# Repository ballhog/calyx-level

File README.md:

# Calyx-Level

Wired, fail-safe auto top-off (ATO) for a reef system. Part of the Corallite **Calyx** family
(wired connected devices: Calyx-Outlet, Calyx-Sense, Calyx-Level).

Built for Joe's own tank first. Each step should be useful on its own; it becomes a product only if it proves itself.

## In one paragraph

A **sensor node** at the sump reads the water level and the RO reservoir, and while water is needed it keeps
handing a short **run permission (lease)** over Ethernet to a **pump node** at the RO station. The pump node runs
the pump only while it holds a fresh lease and stays inside its own limits (run time, off time, daily volume).
Anything that breaks (cable, switch, either node, firmware) makes the lease run out and the pump stop. A
**hardwired high-level float** cuts pump power in series, with no firmware or network in the path. Both nodes are
Olimex ESP32-POE-ISO boards on a blank Arduino Uno proto shield, so off-the-shelf Uno shields plug straight in.

## Docs

| Doc | What's in it |
|---|---|
| [docs/design.md](docs/design.md) | How it works: roles, lease protocol, limits, sensor health, failure table, reporting |
| [docs/parts.md](docs/parts.md) | Parts list (bench build and per node), with what's already on hand |
| [docs/schematic.md](docs/schematic.md) | Wiring, pin map (Uno names ↔ ESP32 GPIO), input/output circuits, power |
| [docs/provisioning.md](docs/provisioning.md) | First flash, node role and id, Coeno OTA, publishing builds |
| [hardware/DESIGN.md](hardware/DESIGN.md) | KiCad carrier rev A: schematic, PCB, build options, checks before ordering |

## Status (2026-10-26)

Carrier PCB rev A designed (schematic + routed board, DRC copper-clean; see hardware/DESIGN.md). No firmware yet. Coeno already serves `/firmware/calyx-level/latest.json` (Coeno `b9fa573`).

## Related

- Corallite project docs: *Corallite ATO - architecture 2026-10-22* (the decisions this repo implements),
  *Corallite doser - E4 controller 2026-10-22*, *Salt swap doser - parked 2026-10-20*.
- [ballhog/calyx-sense](https://github.com/ballhog/calyx-sense): same board family, same OTA client.
- Coeno `firmware/calyx-level/` and `coeno/api/routes/firmware.py`: the OTA server.

## Rules that don't bend

1. Safety lives on the boxes. Xanthe and Coeno read and alert; they never switch the pump.
2. The high-level cutoff is hardware in series with pump power. It is never a shield input or a firmware decision.
3. No network message ever means "run". Only a fresh lease does, and silence means stop.

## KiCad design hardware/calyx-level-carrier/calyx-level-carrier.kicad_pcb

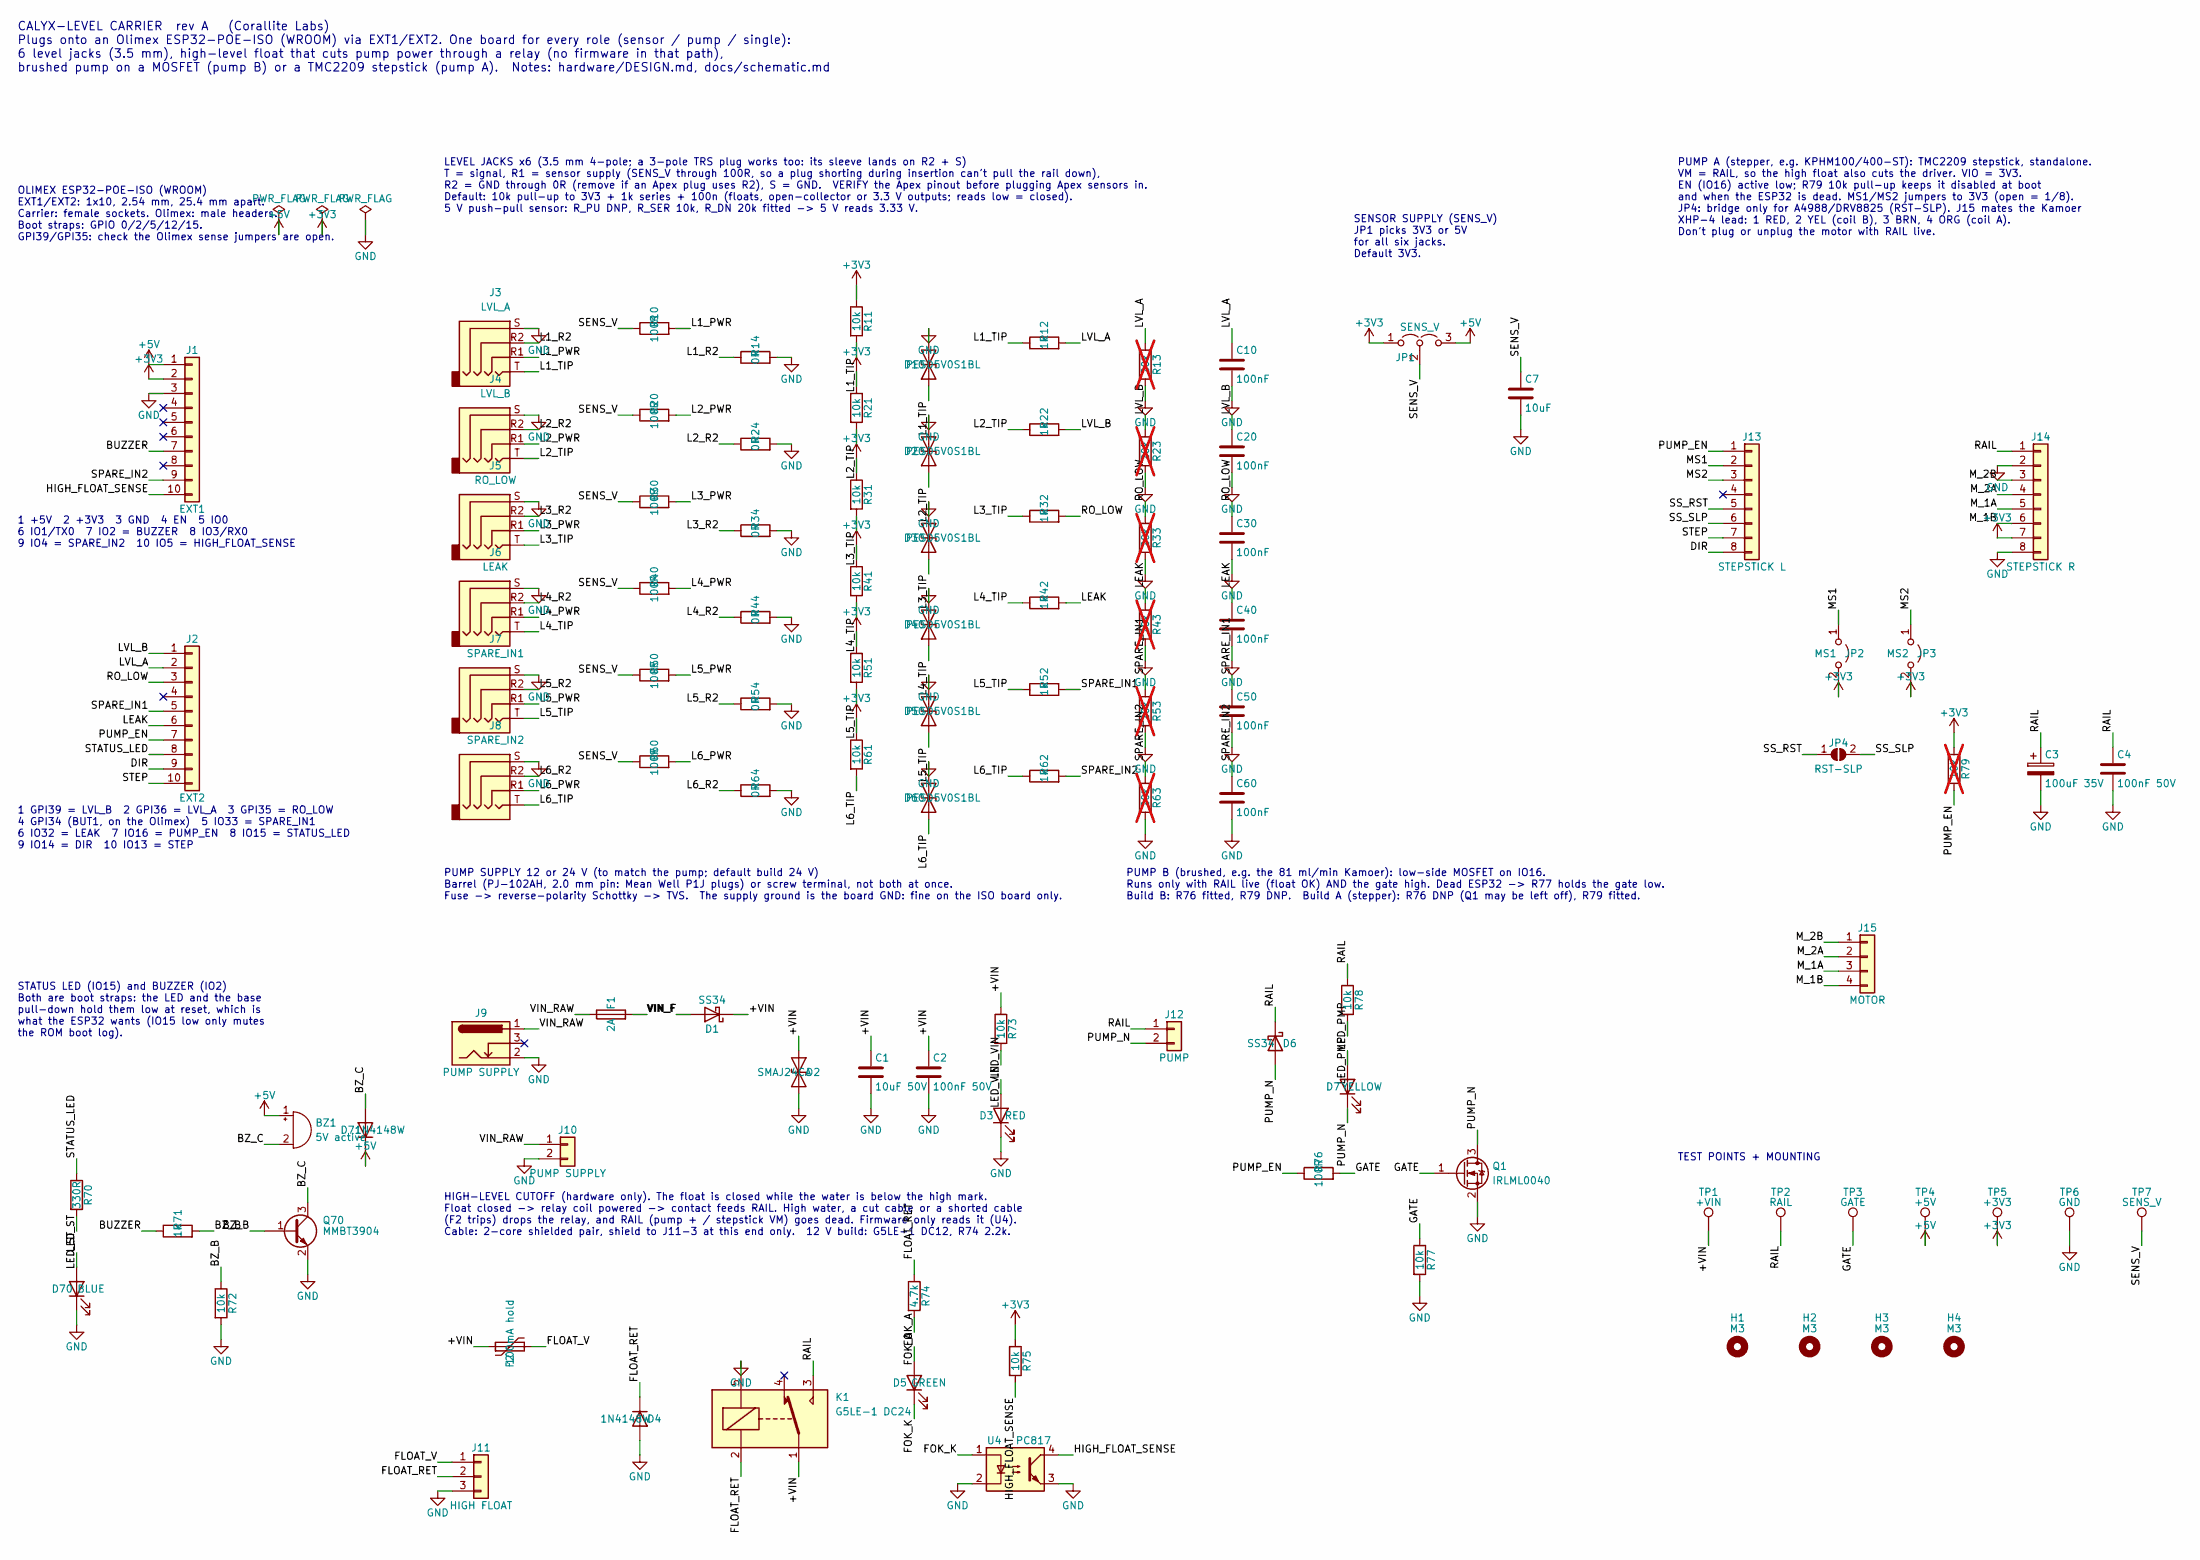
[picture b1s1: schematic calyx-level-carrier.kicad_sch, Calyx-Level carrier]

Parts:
BZ1: 5V active; Buzzer_12x9.5RM7.6; MPN PUI AI-1223-TWT-5V-2-R (verify: 12 mm, 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
C1: 10uF 50V; C_1206_3216Metric_Pad1.33x1.80mm_HandSolder
C2, C4: 100nF 50V; C_0603_1608Metric_Pad1.08x0.95mm_HandSolder
C3: 100uF 35V; CP_Radial_D6.3mm_P2.50mm
C7: 10uF; C_0805_2012Metric_Pad1.18x1.45mm_HandSolder
C10, C20, C30, C40, C50, C60: 100nF; C_0603_1608Metric_Pad1.08x0.95mm_HandSolder
D1, D6: SS34; D_SMA; MPN SS34
D2: SMAJ24CA; D_SMA; MPN SMAJ24CA
D3: RED; LED_0603_1608Metric
D4, D71: 1N4148W; D_SOD-123
D5: GREEN; LED_0603_1608Metric
D7: YELLOW; LED_0603_1608Metric
D10, D20, D30, D40, D50, D60: PESD5V0S1BL; D_SOD-323; MPN PESD5V0S1BL
D70: BLUE; LED_0603_1608Metric
F1: 2A; Fuseholder_Littelfuse_Nano2_154x; MPN Littelfuse 0154002.DRT holder + 0453002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
F2: 100mA hold; Fuse_1812_4532Metric; MPN Bourns MF-MSMF010-2 (0.1 A, 60 V)
H1, H2, H3, H4: M3; MountingHole_3.2mm_M3
J1: EXT1; PinSocket_1x10_P2.54mm_Vertical
J2: EXT2; PinSocket_1x10_P2.54mm_Vertical
J3: LVL_A; Jack_3.5mm_KoreanHropartsElec_PJ-320D-4A_Horizontal; MPN PJ-320D-4A; LCSC C95562
J4: LVL_B; Jack_3.5mm_KoreanHropartsElec_PJ-320D-4A_Horizontal; MPN PJ-320D-4A; LCSC C95562
J5: RO_LOW; Jack_3.5mm_KoreanHropartsElec_PJ-320D-4A_Horizontal; MPN PJ-320D-4A; LCSC C95562
J6: LEAK; Jack_3.5mm_KoreanHropartsElec_PJ-320D-4A_Horizontal; MPN PJ-320D-4A; LCSC C95562
J7: SPARE_IN1; Jack_3.5mm_KoreanHropartsElec_PJ-320D-4A_Horizontal; MPN PJ-320D-4A; LCSC C95562
J8: SPARE_IN2; Jack_3.5mm_KoreanHropartsElec_PJ-320D-4A_Horizontal; MPN PJ-320D-4A; LCSC C95562
J9: PUMP SUPPLY; BarrelJack_CUI_PJ-102AH_Horizontal; MPN PJ-102AH
J10: PUMP SUPPLY; TerminalBlock_Phoenix_MKDS-1,5-2-5.08_1x02_P5.08mm_Horizont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; MPN MKDS 1,5/2-5,08 (1715721)
J11: HIGH FLOAT; TerminalBlock_Phoenix_MKDS-1,5-3-5.08_1x03_P5.08mm_Horizont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; MPN MKDS 1,5/3-5,08 (1715734)
J12: PUMP; TerminalBlock_Phoenix_MKDS-1,5-2-5.08_1x02_P5.08mm_Horizont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; MPN MKDS 1,5/2-5,08 (1715721)
J13: STEPSTICK L; PinSocket_1x08_P2.54mm_Vertical
J14: STEPSTICK R; PinSocket_1x08_P2.54mm_Vertical
J15: MOTOR; JST_XH_B4B-XH-A_1x04_P2.50mm_Vertical; MPN B4B-XH-A
JP1: SENS_V; PinHeader_1x03_P2.54mm_Vertical
JP2: MS1; PinHeader_1x02_P2.54mm_Vertical
JP3: MS2; PinHeader_1x02_P2.54mm_Vertical
JP4: RST-SLP; SolderJumper-2_P1.3mm_Open_RoundedPad1.0x1.5mm
K1: G5LE-1 DC24; Relay_SPDT_Omron-G5LE-1; MPN G5LE-1 DC24
Q1: IRLML0040; SOT-23; MPN IRLML0040TRPBF
Q70: MMBT3904; SOT-23
R10, R20, R30, R40, R50, R60, R76: 100R; R_0603_1608Metric_Pad0.98x0.95mm_HandSolder
R11, R21, R31, R41, R51, R61, R72, R73, R75, R77, R78: 10k; R_0603_1608Metric_Pad0.98x0.95mm_HandSolder
R12, R22, R32, R42, R52, R62, R71: 1k; R_0603_1608Metric_Pad0.98x0.95mm_HandSolder
R13, R23, R33, R43, R53, R63: 20k; R_0603_1608Metric_Pad0.98x0.95mm_HandSolder; not fitted
R14, R24, R34, R44, R54, R64: 0R; R_0603_1608Metric_Pad0.98x0.95mm_HandSolder
R70: 330R; R_0603_1608Metric_Pad0.98x0.95mm_HandSolder
R74: 4.7k; R_1206_3216Metric_Pad1.30x1.75mm_HandSolder
R79: 10k; R_0603_1608Metric_Pad0.98x0.95mm_HandSolder; not fitted
TP1: +VIN; TestPoint_Pad_D1.5mm
TP2: RAIL; TestPoint_Pad_D1.5mm
TP3: GATE; TestPoint_Pad_D1.5mm
TP4: +5V; TestPoint_Pad_D1.5mm
TP5: +3V3; TestPoint_Pad_D1.5mm
TP6: GND; TestPoint_Pad_D1.5mm
TP7: SENS_V; TestPoint_Pad_D1.5mm
U4: PC817; SMDIP-4_W9.53mm; MPN PC817 SMD gull-wing (verify lead span)

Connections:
+3V3: J1.2, J14.7, JP1.1 (A), JP2.2 (B), JP3.2 (B), R11.1, R21.1, R31.1, R41.1, R51.1, R61.1, R75.1, R79.1, TP5.1
+5V: BZ1.1 (+), D71.1 (K), J1.1, JP1.3 (B), TP4.1
/+VIN: C1.1, C2.1, D1.1 (K), D2.1 (A1), F2.1, K1.1, R73.1, TP1.1
/BUZZER: J1.7, R71.1
/BZ_B: Q70.1 (B), R71.2, R72.1
/BZ_C: BZ1.2 (-), D71.2 (A), Q70.3 (C)
/DIR: J2.9, J13.8
/FLOAT_RET: D4.1 (K), J11.2, K1.2, R74.1
/FLOAT_V: F2.2, J11.1
/FOK_A: D5.2 (A), R74.2
/FOK_K: D5.1 (K), U4.1
/GATE: Q1.1 (G), R76.2, R77.1, TP3.1
/HIGH_FLOAT_SENSE: J1.10, R75.2, U4.4
/L1_PWR: J3.R1, R10.2
/L1_R2: J3.R2, R14.1
/L1_TIP: D10.1 (A1), J3.T, R11.2, R12.1
/L2_PWR: J4.R1, R20.2
/L2_R2: J4.R2, R24.1
/L2_TIP: D20.1 (A1), J4.T, R21.2, R22.1
/L3_PWR: J5.R1, R30.2
/L3_R2: J5.R2, R34.1
/L3_TIP: D30.1 (A1), J5.T, R31.2, R32.1
/L4_PWR: J6.R1, R40.2
/L4_R2: J6.R2, R44.1
/L4_TIP: D40.1 (A1), J6.T, R41.2, R42.1
/L5_PWR: J7.R1, R50.2
/L5_R2: J7.R2, R54.1
/L5_TIP: D50.1 (A1), J7.T, R51.2, R52.1
/L6_PWR: J8.R1, R60.2
/L6_R2: J8.R2, R64.1
/L6_TIP: D60.1 (A1), J8.T, R61.2, R62.1
/LEAK: C40.1, J2.6, R42.2, R43.1
/LED_PMP: D7.2 (A), R78.2
/LED_ST: D70.2 (A), R70.2
/LED_VIN: D3.2 (A), R73.2
/LVL_A: C10.1, J2.2, R12.2, R13.1
/LVL_B: C20.1, J2.1, R22.2, R23.1
/MS1: J13.2, JP2.1 (A)
/MS2: J13.3, JP3.1 (A)
/M_1A: J14.5, J15.3
/M_1B: J14.6, J15.4
/M_2A: J14.4, J15.2
/M_2B: J14.3, J15.1
/PUMP_EN: J2.7, J13.1, R76.1, R79.2
/PUMP_N: D6.2 (A), D7.1 (K), J12.2, Q1.3 (D)
/RAIL: C3.1, C4.1, D6.1 (K), J12.1, J14.1, K1.3, R78.1, TP2.1
/RO_LOW: C30.1, J2.3, R32.2, R33.1
/SENS_V: C7.1, JP1.2 (C), R10.1, R20.1, R30.1, R40.1, R50.1, R60.1, TP7.1
/SPARE_IN1: C50.1, J2.5, R52.2, R53.1
/SPARE_IN2: C60.1, J1.9, R62.2, R63.1
/SS_RST: J13.5, JP4.1 (A)
/SS_SLP: J13.6, JP4.2 (B)
/STATUS_LED: J2.8, R70.1
/STEP: J2.10, J13.7
/VIN_F: D1.2 (A), F1.2
/VIN_RAW: F1.1, J9.1, J10.1
GND: C1.2, C2.2, C3.2, C4.2, C7.2, C10.2, C20.2, C30.2, C40.2, C50.2, C60.2, D2.2 (A2), D3.1 (K), D4.2 (A), D10.2 (A2), D20.2 (A2), D30.2 (A2), D40.2 (A2), D50.2 (A2), D60.2 (A2), D70.1 (K), J1.3, J3.S, J4.S, J5.S, J6.S, J7.S, J8.S, J9.2, J10.2, J11.3, J14.2, J14.8, K1.5, Q1.2 (S), Q70.2 (E), R13.2, R14.2, R23.2, R24.2, R33.2, R34.2, R43.2, R44.2, R53.2, R54.2, R63.2, R64.2, R72.2, R77.2, TP6.1, U4.2, U4.3

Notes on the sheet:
CALYX-LEVEL CARRIER rev A (Corallite Labs) Plugs onto an Olimex ESP32-POE-ISO (WROOM) via EXT1/EXT2. One board for every role (sensor / pump / single): 6 level jacks (3.5 mm), high-level float that cuts pump power through a relay (no firmware in that path), brushed pump on a MOSFET (pump B) or a TM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
OLIMEX ESP32-POE-ISO (WROOM) EXT1/EXT2: 1x10, 2.54 mm, 25.4 mm apart. Carrier: female sockets. Olimex: male headers. Boot straps: GPIO 0/2/5/12/15. GPI39/GPI35: check the Olimex sense jumpers are open.
1 +5V 2 +3V3 3 GND 4 EN 5 IO0 6 IO1/TX0 7 IO2 = BUZZER 8 IO3/RX0 9 IO4 = SPARE_IN2 10 IO5 = HIGH_FLOAT_SENSE
1 GPI39 = LVL_B 2 GPI36 = LVL_A 3 GPI35 = RO_LOW 4 GPI34 (BUT1, on the Olimex) 5 IO33 = SPARE_IN1 6 IO32 = LEAK 7 IO16 = PUMP_EN 8 IO15 = STATUS_LED 9 IO14 = DIR 10 IO13 = STEP
LEVEL JACKS x6 (3.5 mm 4-pole; a 3-pole TRS plug works too: its sleeve lands on R2 + S) T = signal, R1 = sensor supply (SENS_V through 100R, so a plug shorting during insertion can't pull the rail down), R2 = GND through 0R (remove if an Apex plug uses R2), S = GND. VERIFY the Apex pinout before pl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
SENSOR SUPPLY (SENS_V) JP1 picks 3V3 or 5V for all six jacks. Default 3V3.
STATUS LED (IO15) and BUZZER (IO2) Both are boot straps: the LED and the base pull-down hold them low at reset, which is what the ESP32 wants (IO15 low only mutes the ROM boot log).
PUMP SUPPLY 12 or 24 V (to match the pump; default build 24 V) Barrel (PJ-102AH, 2.0 mm pin: Mean Well P1J plugs) or screw terminal, not both at once. Fuse -> reverse-polarity Schottky -> TVS. The supply ground is the board GND: fine on the ISO board only.
HIGH-LEVEL CUTOFF (hardware only). The float is closed while the water is below the high mark. Float closed -> relay coil powered -> contact feeds RAIL. High water, a cut cable or a shorted cable (F2 trips) drops the relay, and RAIL (pump + / stepstick VM) goes dead. Firmware only reads it (U4). Ca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
PUMP B (brushed, e.g. the 81 ml/min Kamoer): low-side MOSFET on IO16. Runs only with RAIL live (float OK) AND the gate high. Dead ESP32 -> R77 holds the gate low. Build B: R76 fitted, R79 DNP. Build A (stepper): R76 DNP (Q1 may be left off), R79 fitted.
PUMP A (stepper, e.g. KPHM100/400-ST): TMC2209 stepstick, standalone. VM = RAIL, so the high float also cuts the driver. VIO = 3V3. EN (IO16) active low; R79 10k pull-up keeps it disabled at boot and when the ESP32 is dead. MS1/MS2 jumpers to 3V3 (open = 1/8). JP4: bridge only for A4988/DRV8825 (RS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
TEST POINTS + MOUNTING

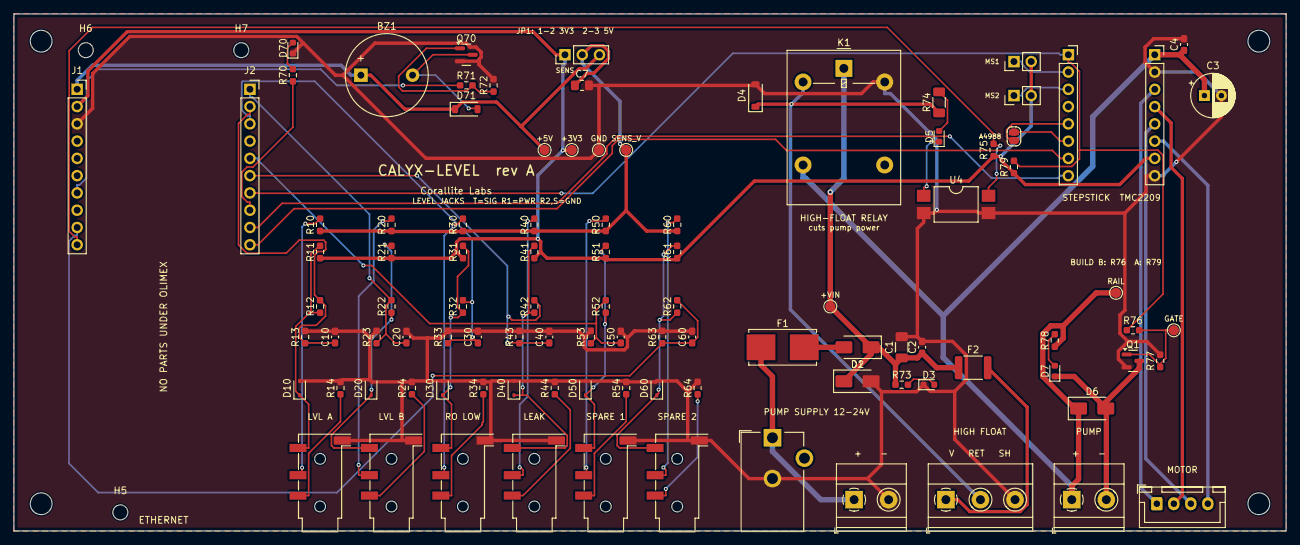
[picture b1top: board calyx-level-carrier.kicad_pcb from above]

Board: 2 copper layers, 187.0 x 76.0 mm, 106 parts (0 on the bottom side), 57 nets.

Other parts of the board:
H5: Olimex MH1 standoff; MountingHole_2.2mm_M2
H6: Olimex MH2 standoff; MountingHole_2.2mm_M2
H7: Olimex MH3 standoff; MountingHole_2.2mm_M2

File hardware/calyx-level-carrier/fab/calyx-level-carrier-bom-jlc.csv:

Comment,Designator,Footprint,LCSC Part #,MPN
5V active,BZ1,Buzzer_12x9.5RM7.6,,"PUI AI-1223-TWT-5V-2-R (verify: 12 mm, 7.6 mm pitch, active 5 V)"
10uF 50V,C1,C_1206_3216Metric_Pad1.33x1.80mm_HandSolder,,
100nF,"C10,C20,C30,C40,C50,C60",C_0603_1608Metric_Pad1.08x0.95mm_HandSolder,,
100nF 50V,"C2,C4",C_0603_1608Metric_Pad1.08x0.95mm_HandSolder,,
100uF 35V,C3,CP_Radial_D6.3mm_P2.50mm,,
10uF,C7,C_0805_2012Metric_Pad1.18x1.45mm_HandSolder,,
SS34,"D1,D6",D_SMA,,SS34
PESD5V0S1BL,"D10,D20,D30,D40,D50,D60",D_SOD-323,,PESD5V0S1BL
SMAJ24CA,D2,D_SMA,,SMAJ24CA
RED,D3,LED_0603_1608Metric,,
1N4148W,"D4,D71",D_SOD-123,,
GREEN,D5,LED_0603_1608Metric,,
YELLOW,D7,LED_0603_1608Metric,,
BLUE,D70,LED_0603_1608Metric,,
2A,F1,Fuseholder_Littelfuse_Nano2_154x,,Littelfuse 0154002.DRT holder + 0453002.MR fuse (verify)
100mA hold,F2,Fuse_1812_4532Metric,,"Bourns MF-MSMF010-2 (0.1 A, 60 V)"
EXT1,J1,PinSocket_1x10_P2.54mm_Vertical,,
PUMP SUPPLY,J10,"TerminalBlock_Phoenix_MKDS-1,5-2-5.08_1x02_P5.08mm_Horizontal",,"MKDS 1,5/2-5,08 (1715721)"
HIGH FLOAT,J11,"TerminalBlock_Phoenix_MKDS-1,5-3-5.08_1x03_P5.08mm_Horizontal",,"MKDS 1,5/3-5,08 (1715734)"
PUMP,J12,"TerminalBlock_Phoenix_MKDS-1,5-2-5.08_1x02_P5.08mm_Horizontal",,"MKDS 1,5/2-5,08 (1715721)"
STEPSTICK L,J13,PinSocket_1x08_P2.54mm_Vertical,,
STEPSTICK R,J14,PinSocket_1x08_P2.54mm_Vertical,,
MOTOR,J15,JST_XH_B4B-XH-A_1x04_P2.50mm_Vertical,,B4B-XH-A
EXT2,J2,PinSocket_1x10_P2.54mm_Vertical,,
LVL_A,J3,Jack_3.5mm_KoreanHropartsElec_PJ-320D-4A_Horizontal,C95562,
LVL_B,J4,Jack_3.5mm_KoreanHropartsElec_PJ-320D-4A_Horizontal,C95562,
RO_LOW,J5,Jack_3.5mm_KoreanHropartsElec_PJ-320D-4A_Horizontal,C95562,
LEAK,J6,Jack_3.5mm_KoreanHropartsElec_PJ-320D-4A_Horizontal,C95562,
SPARE_IN1,J7,Jack_3.5mm_KoreanHropartsElec_PJ-320D-4A_Horizontal,C95562,
SPARE_IN2,J8,Jack_3.5mm_KoreanHropartsElec_PJ-320D-4A_Horizontal,C95562,
PUMP SUPPLY,J9,BarrelJack_CUI_PJ-102AH_Horizontal,,PJ-102AH
SENS_V,JP1,PinHeader_1x03_P2.54mm_Vertical,,
MS1,JP2,PinHeader_1x02_P2.54mm_Vertical,,
MS2,JP3,PinHeader_1x02_P2.54mm_Vertical,,
RST-SLP,JP4,SolderJumper-2_P1.3mm_Open_RoundedPad1.0x1.5mm,,
G5LE-1 DC24,K1,Relay_SPDT_Omron-G5LE-1,,G5LE-1 DC24
IRLML0040,Q1,SOT-23,,IRLML0040TRPBF
MMBT3904,Q70,SOT-23,,
100R,"R10,R20,R30,R40,R50,R60,R76",R_0603_1608Metric_Pad0.98x0.95mm_HandSolder,,
10k,"R11,R21,R31,R41,R51,R61,R72,R73,R75,R77,R78",R_0603_1608Metric_Pad0.98x0.95mm_HandSolder,,
1k,"R12,R22,R32,R42,R52,R62,R71",R_0603_1608Metric_Pad0.98x0.95mm_HandSolder,,
0R,"R14,R24,R34,R44,R54,R64",R_0603_1608Metric_Pad0.98x0.95mm_HandSolder,,
330R,R70,R_0603_1608Metric_Pad0.98x0.95mm_HandSolder,,
4.7k,R74,R_1206_3216Metric_Pad1.30x1.75mm_HandSolder,,
PC817,U4,SMDIP-4_W9.53mm,,PC817 SMD gull-wing (verify lead span)

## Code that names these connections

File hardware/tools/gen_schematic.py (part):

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               {'T': tip, 'R1': pwr, 'R2': r2, 'S': 'GND'},
               fields={'Footprint': 'Connector_Audio:Jack_3.5mm_KoreanHropartsElec_PJ-320D-4A_Horizontal',
                       'LCSC': 'C95562', 'MPN': 'PJ-320D-4A', 'Manufacturer': 'Korean Hroparts Elec'})
        s.part('Device', 'R', 'R%d' % (b + 0), '100R', 132.08, y0 - 2.54, {'1': 'SENS_V', '2': pwr}, angle=90,
               fields={'Footprint': R0603, 'Notes': 'R_PWR: limits a ring-to-sleeve short while a plug goes in'})
        s.part('Device', 'R', 'R%d' % (b + 4), '0R', 149.86, y0 + 2.54, {'1': r2, '2': 'GND'}, angle=90,
               fields={'Footprint': R0603, 'Notes': 'R2 link: jack ring 2 to GND; remove if a sensor plug uses R2'})
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    T('STATUS LED (IO15) and BUZZER (IO2)\nBoth are boot straps: the LED and the base\npull-down hold them low at reset, which is\nwhat the ESP32 wants (IO15 low only mutes\nthe ROM boot log).', 20, 185)
    s.part('Device', 'R', 'R70', '330R', 30.48, 222.25, {'1': 'STATUS_LED', '2': 'LED_ST'},
           fields={'Footprint': R0603})
    s.part('Device', 'LED', 'D70', 'BLUE', 30.48, 238.76, {'2': 'LED_ST', '1': 'GND'}, angle=90,
           fields={'Footprint': LED0603, 'Notes': 'status'})
    s.part('Device', 'R', 'R71', '1k', 48.26, 228.6, {'1': 'BUZZER', '2': 'BZ_B'}, angle=90,
           fields={'Footprint': R0603})
    s.part('Device', 'R', 'R72', '10k', 55.88, 241.3, {'1': 'BZ_B', '2': 'GND'}, fields={'Footprint': R0603})
    s.part('Transistor_BJT', 'MMBT3904', 'Q70', 'MMBT3904', 68.58, 228.6, {'1': 'BZ_B', '2': 'GND', '3': 'BZ_C'},
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    s.part('Device', 'Buzzer', 'BZ1', '5V active', 68.58, 210.82, {'1': '+5V', '2': 'BZ_C'},
           fields={'Footprint': 'Buzzer_Beeper:Buzzer_12x9.5RM7.6',
                   'MPN': 'PUI AI-1223-TWT-5V-2-R (verify: 12 mm, 7.6 mm pitch, active 5 V)'})
    s.part('Device', 'D', 'D71', '1N4148W', 81.28, 210.82, {'1': '+5V', '2': 'BZ_C'}, angle=90,
           fields={'Footprint': SOD123})

    # ================= D: pump supply input (x 95-210, y 165-210)
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                   'Manufacturer': 'Same Sky (CUI)'})
    s.part('Connector_Generic', 'Conn_01x02', 'J10', 'PUMP SUPPLY', 116.84, 213.36, {'1': 'VIN_RAW', '2': 'GND'},
           fields={'Footprint': MKDS2, 'MPN': 'MKDS 1,5/2-5,08 (1715721)', 'Manufacturer': 'Phoenix Contact'})
    s.part('Device', 'Fuse', 'F1', '2A', 124.46, 190.5, {'1': 'VIN_RAW', '2': 'VIN_F'}, angle=90,
           fields={'Footprint': 'Fuse:Fuseholder_Littelfuse_Nano2_154x',
                   'MPN': 'Littelfuse 0154002.DRT holder + 0453002.MR fuse (verify)'})
    s.part('Device', 'D_Schottky', 'D1', 'SS34', 142.24, 190.5, {'2': 'VIN_F', '1': '+VIN'}, angle=180,
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    s.part('Device', 'C', 'C2', '100nF 50V', 180.34, 200.66, {'1': '+VIN', '2': 'GND'}, fields={'Footprint': C0603})
    s.part('Device', 'R', 'R73', '10k', 193.04, 193.04, {'1': '+VIN', '2': 'LED_VIN'},
           fields={'Footprint': R0603, 'Notes': '12 V build: 4.7k'})
    s.part('Device', 'LED', 'D3', 'RED', 193.04, 208.28, {'2': 'LED_VIN', '1': 'GND'}, angle=90,
           fields={'Footprint': LED0603, 'Notes': 'pump supply present'})

    # ================= E: high-level float + relay (x 95-210, y 222-285)
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      'Float closed -> relay coil powered -> contact feeds RAIL. High water, a cut cable or a shorted cable\n'
      '(F2 trips) drops the relay, and RAIL (pump + / stepstick VM) goes dead. Firmware only reads it (U4).\n'
      'Cable: 2-core shielded pair, shield to J11-3 at this end only.  12 V build: G5LE-1 DC12, R74 2.2k.', 95, 222)
    s.part('Device', 'Polyfuse', 'F2', '100mA hold', 106.68, 248.92, {'1': '+VIN', '2': 'FLOAT_V'}, angle=90,
           fields={'Footprint': 'Fuse:Fuse_1812_4532Metric', 'MPN': 'Bourns MF-MSMF010-2 (0.1 A, 60 V)'})
    s.part('Connector_Generic', 'Conn_01x03', 'J11', 'HIGH FLOAT', 101.6, 271.78,
           {'1': 'FLOAT_V', '2': 'FLOAT_RET', '3': 'GND'},
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           fields={'Footprint': SOD123, 'Notes': 'coil flyback'})
    s.part('Device', 'R', 'R74', '4.7k', 177.8, 240.03, {'1': 'FLOAT_RET', '2': 'FOK_A'},
           fields={'Footprint': R1206, 'Notes': '0.1 W at 24 V: 1206. 12 V build: 2.2k'})
    s.part('Device', 'LED', 'D5', 'GREEN', 177.8, 255.27, {'2': 'FOK_A', '1': 'FOK_K'}, angle=90,
           fields={'Footprint': LED0603, 'Notes': 'FLOAT OK (relay coil powered)'})
    s.part('Isolator', 'PC817', 'U4', 'PC817', 195.58, 270.51,
           {'1': 'FOK_K', '2': 'GND', '4': 'HIGH_FLOAT_SENSE', '3': 'GND'},
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           fields={'Footprint': SMA, 'MPN': 'SS34', 'Notes': 'motor flyback'})
    s.part('Device', 'R', 'R78', '10k', 254.0, 187.96, {'1': 'RAIL', '2': 'LED_PMP'},
           fields={'Footprint': R0603, 'Notes': '12 V build: 4.7k'})
    s.part('Device', 'LED', 'D7', 'YELLOW', 254.0, 203.2, {'2': 'LED_PMP', '1': 'PUMP_N'}, angle=90,
           fields={'Footprint': LED0603, 'Notes': 'pump energized'})
    s.part('Device', 'Q_NMOS_GSD', 'Q1', 'IRLML0040', 274.32, 218.44, {'1': 'GATE', '2': 'GND', '3': 'PUMP_N'},
           fields={'Footprint': SOT23, 'MPN': 'IRLML0040TRPBF', 'Manufacturer': 'Infineon',
                   'Notes': '40 V 3.6 A, Rds(on) specified at Vgs 2.5 V'})
    s.part('Device', 'R', 'R76', '100R', 248.92, 218.44, {'1': 'PUMP_EN', '2': 'GATE'}, angle=90,
           fields={'Footprint': R0603, 'Notes': 'build B only'})
    s.part('Device', 'R', 'R77', '10k', 266.7, 233.68, {'1': 'GATE', '2': 'GND'}, fields={'Footprint': R0603})

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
